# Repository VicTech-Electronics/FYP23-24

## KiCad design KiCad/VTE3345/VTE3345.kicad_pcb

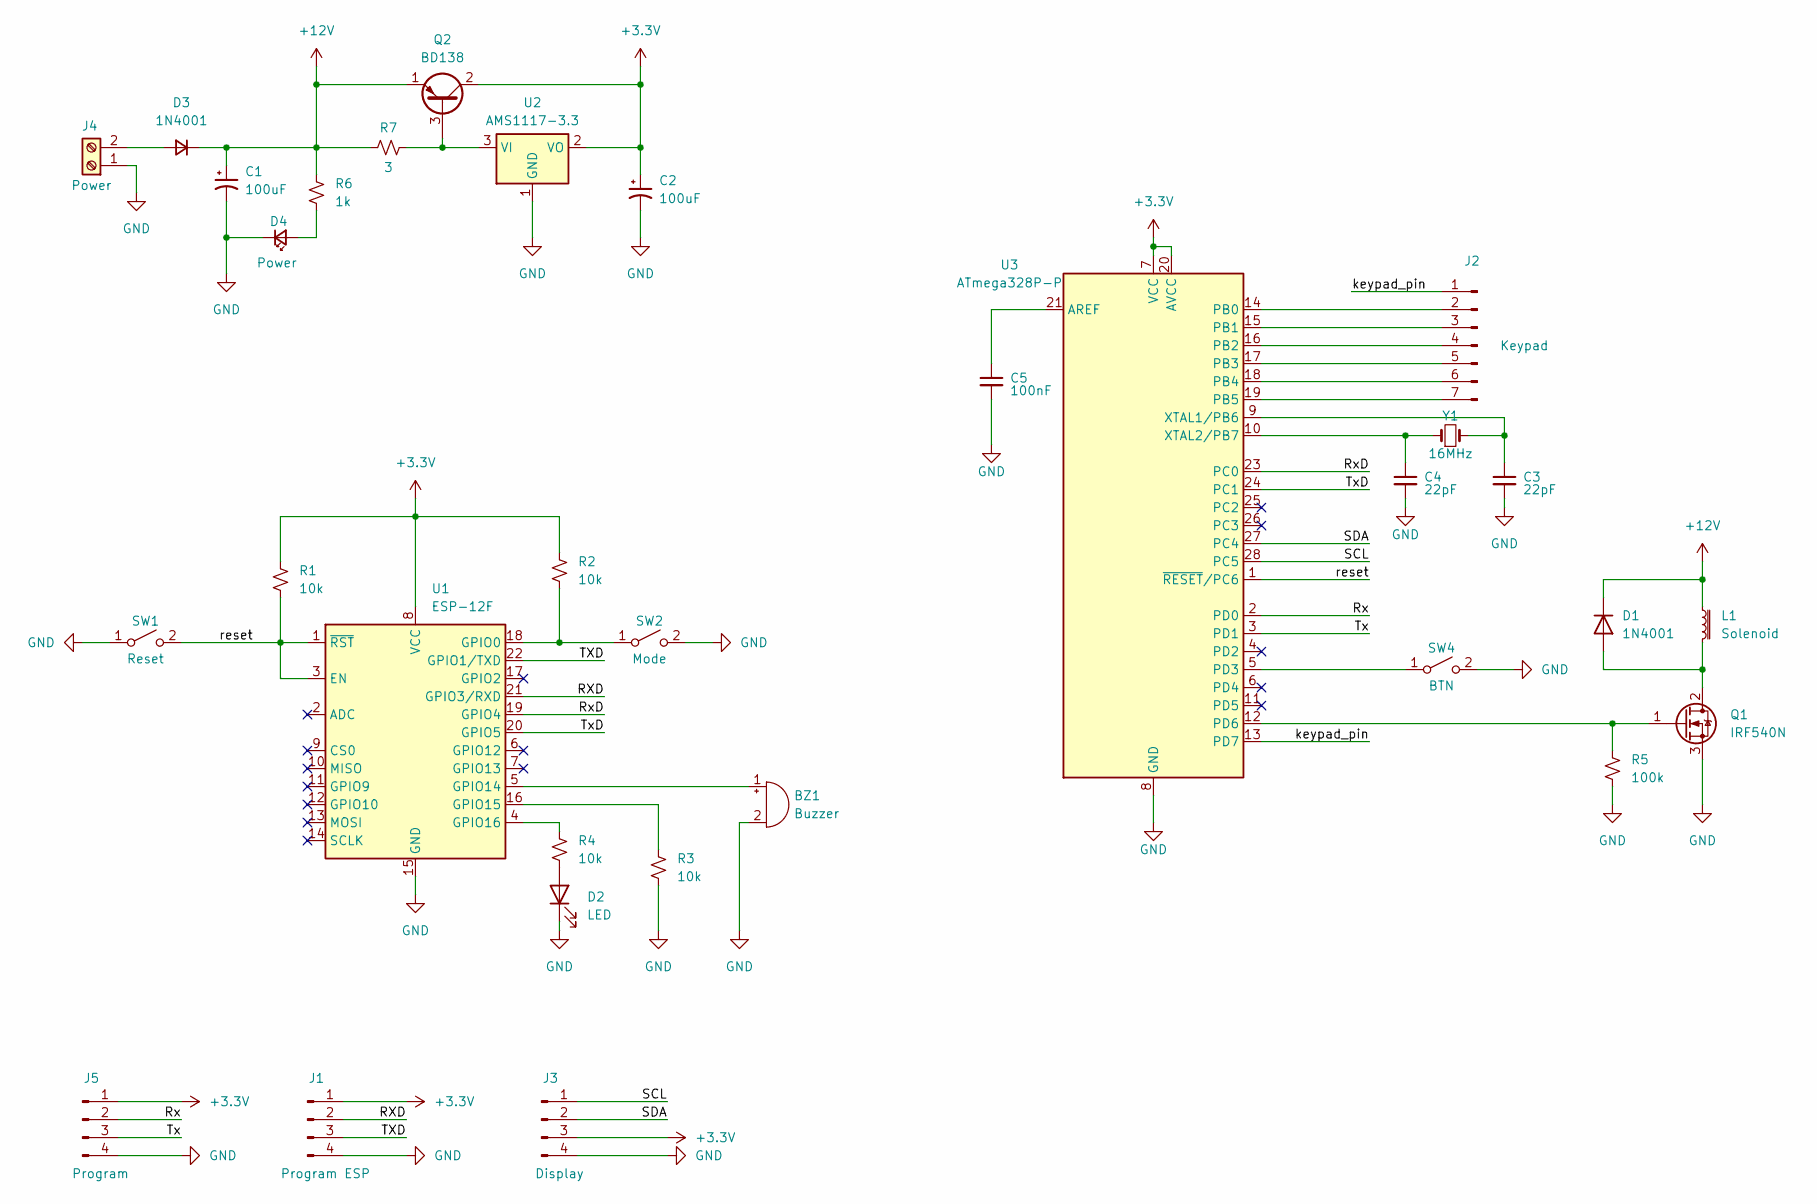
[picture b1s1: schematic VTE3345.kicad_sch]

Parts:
BZ1: Buzzer; Buzzer_12x9.5RM7.6
C1, C2: 100uF; CP_Radial_D5.0mm_P2.50mm
C3, C4: 22pF; C_Disc_D3.0mm_W1.6mm_P2.50mm
C5: 100nF; C_Disc_D3.0mm_W1.6mm_P2.50mm
D1: 1N4001; D_DO-41_SOD81_P10.16mm_Horizontal
D2: LED; LED_D3.0mm
D3: 1N4001; D_A-405_P10.16mm_Horizontal
D4: Power; LED_D3.0mm
J1: Program ESP; PinHeader_1x04_P2.54mm_Vertical
J2: Keypad; PinHeader_1x07_P2.54mm_Vertical
J3: Display; PinHeader_1x04_P2.54mm_Vertical
J4: Power; TerminalBlock_bornier-2_P5.08mm
J5: Program; PinHeader_1x04_P2.54mm_Vertical
L1: Solenoid; TerminalBlock_bornier-2_P5.08mm
Q1: IRF540N; TO-220-3_Vertical
Q2: BD138; TO-126-3_Vertical
R1, R2, R3, R4: 10k; R_Axial_DIN0207_L6.3mm_D2.5mm_P10.16mm_Horizontal
R5: 100k; R_Axial_DIN0207_L6.3mm_D2.5mm_P10.16mm_Horizontal
R6: 1k; R_Axial_DIN0207_L6.3mm_D2.5mm_P10.16mm_Horizontal
R7: 3; R_Axial_DIN0207_L6.3mm_D2.5mm_P10.16mm_Horizontal
SW1: Reset; SW_PUSH_6mm
SW2: Mode; SW_PUSH_6mm
SW4: BTN; TestPoint_2Pads_Pitch2.54mm_Drill0.8mm
U1: ESP-12F; ESP-12E
U2: AMS1117-3.3; SOT-223-3_TabPin2
U3: ATmega328P-P; DIP-28_W7.62mm_LongPads
Y1: 16MHz; Crystal_HC52-U_Vertical

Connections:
+3.3V: C2.1, J1.1, J3.3, J5.1, Q2.2 (C), R1.1, R2.1, U1.8 (VCC), U2.2 (VO), U3.7 (VCC), U3.20 (AVCC)
+12V: C1.1, D1.1 (K), D3.1 (K), L1.1, Q2.1 (E), R6.1, R7.1
/RXD: J1.2, U1.21 (GPIO3/RXD)
/Rx: J5.2, U3.2 (PD0)
/RxD: U1.19 (GPIO4), U3.23 (PC0)
/SCL: J3.1, U3.28 (PC5)
/SDA: J3.2, U3.27 (PC4)
/TXD: J1.3, U1.22 (GPIO1/TXD)
/Tx: J5.3, U3.3 (PD1)
/TxD: U1.20 (GPIO5), U3.24 (PC1)
/keypad_pin: J2.1, U3.13 (PD7)
/reset: R1.2, SW1.2 (B), U1.1 (~RST), U1.3 (EN), U3.1 (~RESET/PC6)
GND: BZ1.2 (-), C1.2, C2.2, C3.2, C4.2, C5.2, D2.1 (K), D4.1 (K), J1.4, J3.4, J4.1, J5.4, Q1.3 (S), R3.2, R5.1, SW1.1 (A), SW2.2 (B), SW4.2 (B), U1.15 (GND), U2.1 (GND), U3.8 (GND), U3.22 (GND)
unnamed: BZ1.1 (+), U1.5 (GPIO14)
unnamed: D1.2 (A), L1.2, Q1.2 (D)
unnamed: D2.2 (A), R4.2
unnamed: D3.2 (A), J4.2
unnamed: D4.2 (A), R6.2
unnamed: J2.2, U3.14 (PB0)
unnamed: J2.3, U3.15 (PB1)
unnamed: J2.4, U3.16 (PB2)
unnamed: J2.5, U3.17 (PB3)
unnamed: J2.6, U3.18 (PB4)
unnamed: J2.7, U3.19 (PB5)
unnamed: Q1.1 (G), R5.2, U3.12 (PD6)
unnamed: Q2.3 (B), R7.2, U2.3 (VI)
unnamed: R2.2, SW2.1 (A), U1.18 (GPIO0)
unnamed: SW4.1 (A), U3.5 (PD3)
unnamed: R3.1, U1.16 (GPIO15)
unnamed: R4.1, U1.4 (GPIO16)
unnamed: C5.1, U3.21 (AREF)
unnamed: C3.1, U3.9 (XTAL1/PB6), Y1.2
unnamed: C4.1, U3.10 (XTAL2/PB7), Y1.1

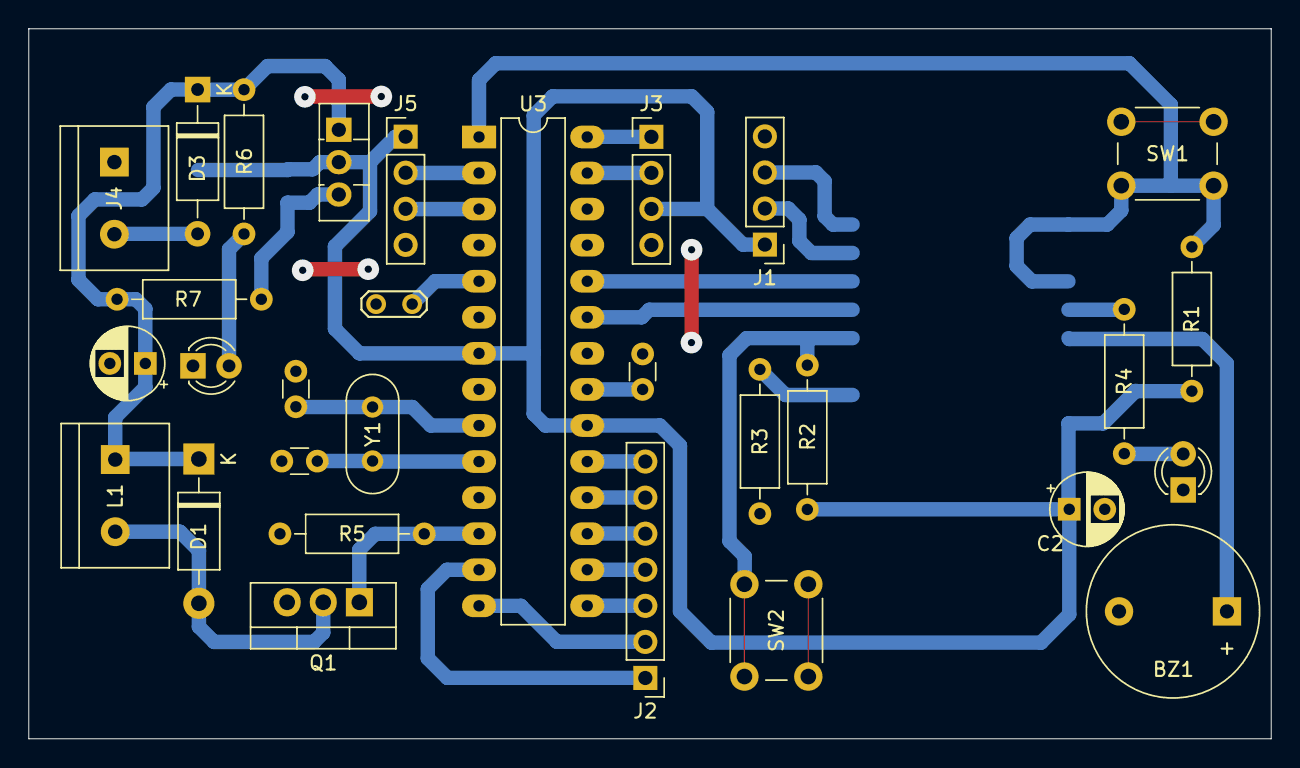
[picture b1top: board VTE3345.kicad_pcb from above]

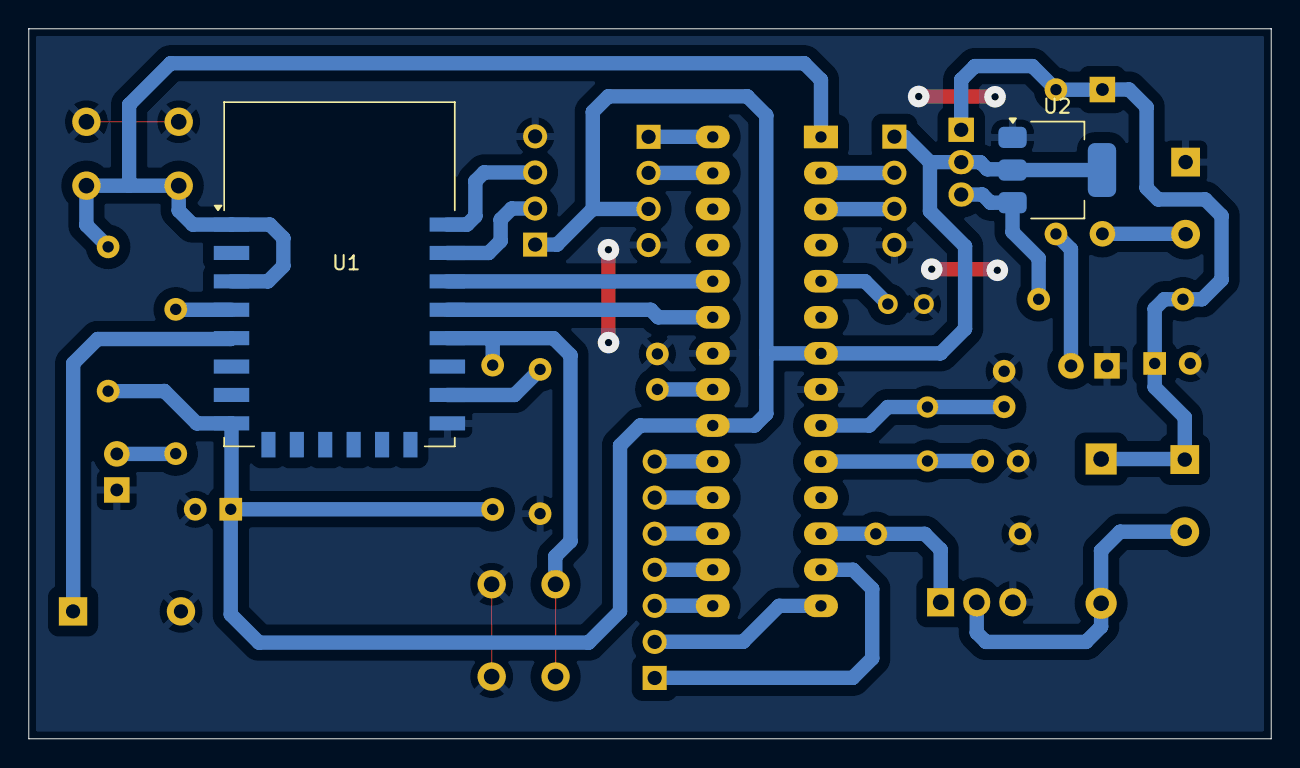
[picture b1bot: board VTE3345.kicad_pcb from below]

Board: 2 copper layers, 87.5 x 50.0 mm, 32 parts (2 on the bottom side), 33 nets.

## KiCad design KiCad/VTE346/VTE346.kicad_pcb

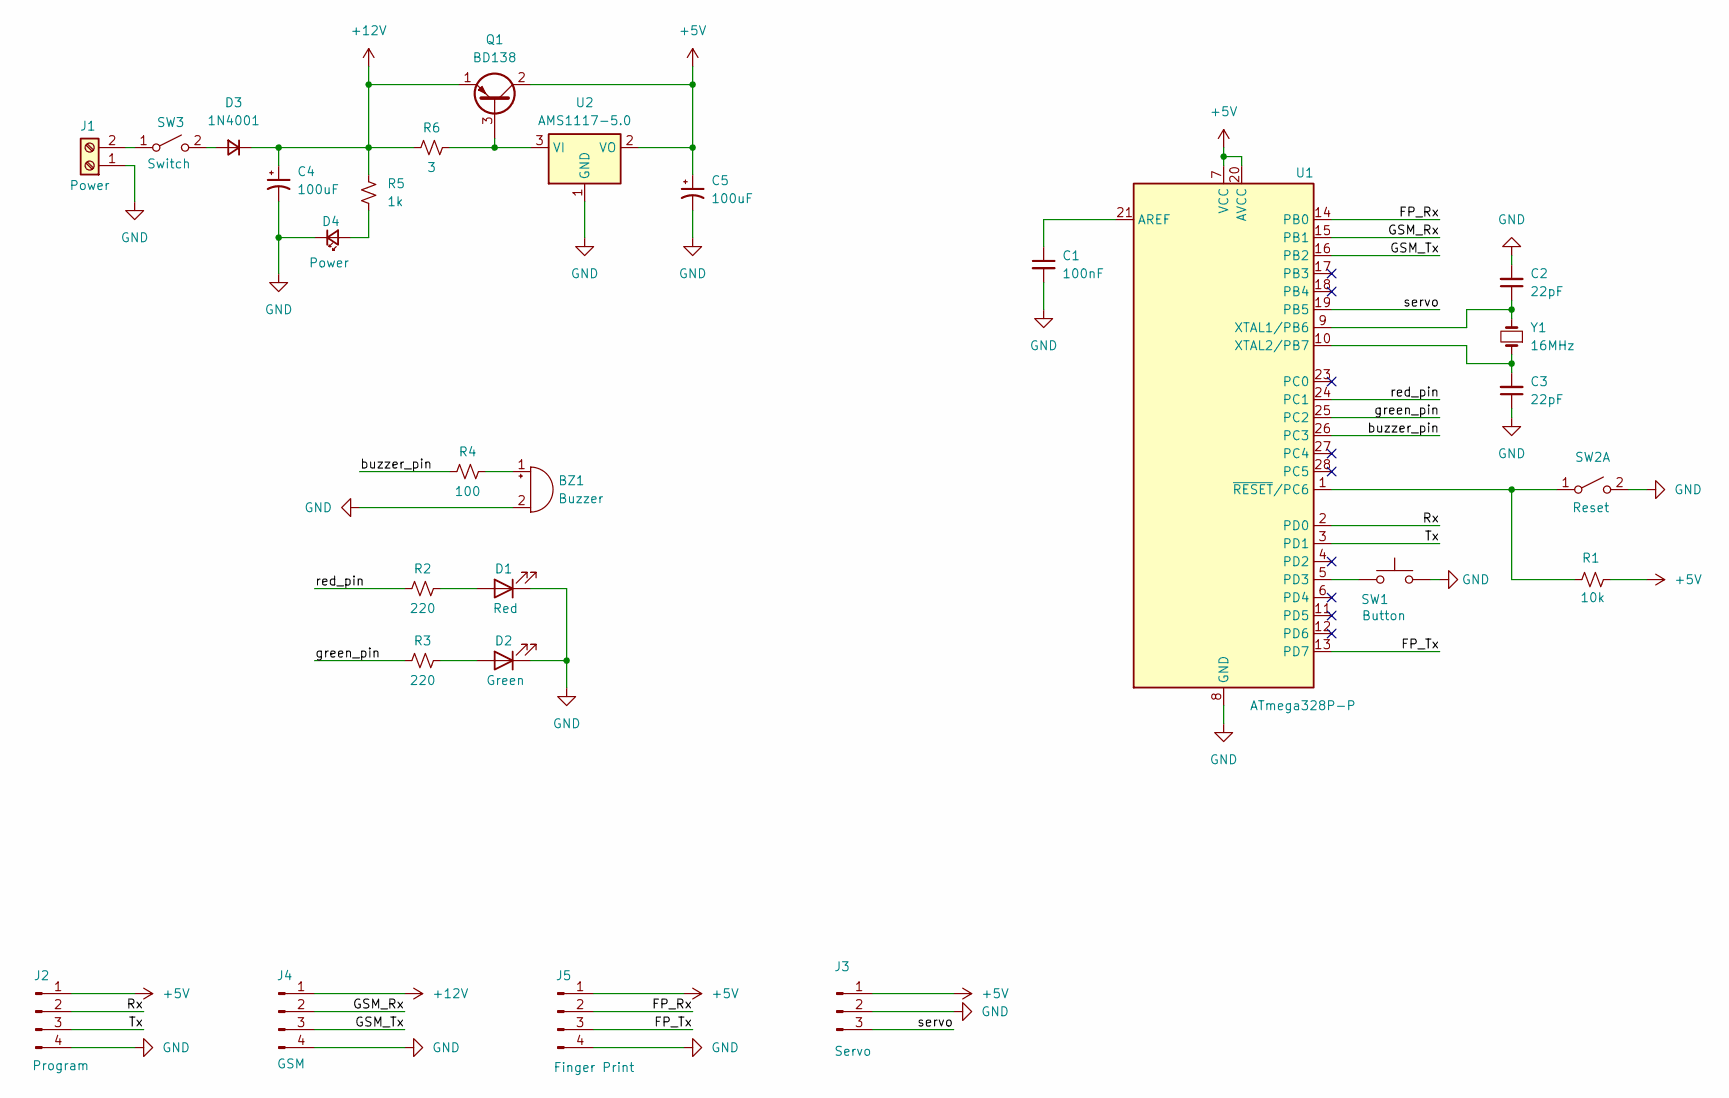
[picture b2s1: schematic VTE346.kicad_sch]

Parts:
BZ1: Buzzer; Buzzer_12x9.5RM7.6
C1: 100nF; C_Disc_D3.0mm_W1.6mm_P2.50mm
C2, C3: 22pF; C_Disc_D3.0mm_W1.6mm_P2.50mm
C4, C5: 100uF; CP_Radial_D5.0mm_P2.50mm
D1: Red; LED_D3.0mm
D2: Green; LED_D3.0mm
D3: 1N4001; D_A-405_P10.16mm_Horizontal
D4: Power; LED_D3.0mm
J1: Power; TerminalBlock_bornier-2_P5.08mm
J2: Program; PinHeader_1x04_P2.54mm_Vertical
J3: Servo; PinHeader_1x03_P2.54mm_Vertical
J4: GSM; PinHeader_1x04_P2.54mm_Vertical
J5: Finger Print; PinHeader_1x04_P2.54mm_Vertical
Q1: BD138; TO-126-3_Vertical
R1: 10k; R_Axial_DIN0207_L6.3mm_D2.5mm_P10.16mm_Horizontal
R2, R3: 220; R_Axial_DIN0207_L6.3mm_D2.5mm_P10.16mm_Horizontal
R4: 100; R_Axial_DIN0207_L6.3mm_D2.5mm_P10.16mm_Horizontal
R5: 1k; R_Axial_DIN0207_L6.3mm_D2.5mm_P10.16mm_Horizontal
R6: 3; R_Axial_DIN0207_L6.3mm_D2.5mm_P10.16mm_Horizontal
SW1: Button; TestPoint_2Pads_Pitch2.54mm_Drill0.8mm
SW2: Reset; SW_PUSH_6mm
SW3: Switch; TestPoint_2Pads_Pitch2.54mm_Drill0.8mm
U1: ATmega328P-P; DIP-28_W7.62mm_Socket_LongPads
U2: AMS1117-5.0; SOT-223-3_TabPin2
Y1: 16MHz; Crystal_HC50_Vertical

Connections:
+5V: C5.1, J2.1, J3.1, J5.1, Q1.2 (C), R1.2, U1.7 (VCC), U1.20 (AVCC), U2.2 (VO)
+12V: C4.1, D3.1 (K), J4.1, Q1.1 (E), R5.1, R6.1
/FP_Rx: J5.2, U1.14 (PB0)
/FP_Tx: J5.3, U1.13 (PD7)
/GSM_Rx: J4.2, U1.15 (PB1)
/GSM_Tx: J4.3, U1.16 (PB2)
/Rx: J2.2, U1.2 (PD0)
/Tx: J2.3, U1.3 (PD1)
/buzzer_pin: R4.1, U1.26 (PC3)
/green_pin: R3.1, U1.25 (PC2)
/red_pin: R2.1, U1.24 (PC1)
/servo: J3.3, U1.19 (PB5)
GND: BZ1.2 (-), C1.2, C2.2, C3.1, C4.2, C5.2, D1.1 (K), D2.1 (K), D4.1 (K), J1.1, J2.4, J3.2, J4.4, J5.4, SW1.2, SW2.2 (B), U1.8 (GND), U1.22 (GND), U2.1 (GND)
unnamed: BZ1.1 (+), R4.2
unnamed: D1.2 (A), R2.2
unnamed: D2.2 (A), R3.2
unnamed: D3.2 (A), SW3.2 (B)
unnamed: D4.2 (A), R5.2
unnamed: J1.2, SW3.1 (A)
unnamed: Q1.3 (B), R6.2, U2.3 (VI)
unnamed: R1.1, SW2.1 (A), U1.1 (~RESET/PC6)
unnamed: C1.1, U1.21 (AREF)
unnamed: SW1.1, U1.5 (PD3)
unnamed: C2.1, U1.9 (XTAL1/PB6), Y1.2
unnamed: C3.2, U1.10 (XTAL2/PB7), Y1.1

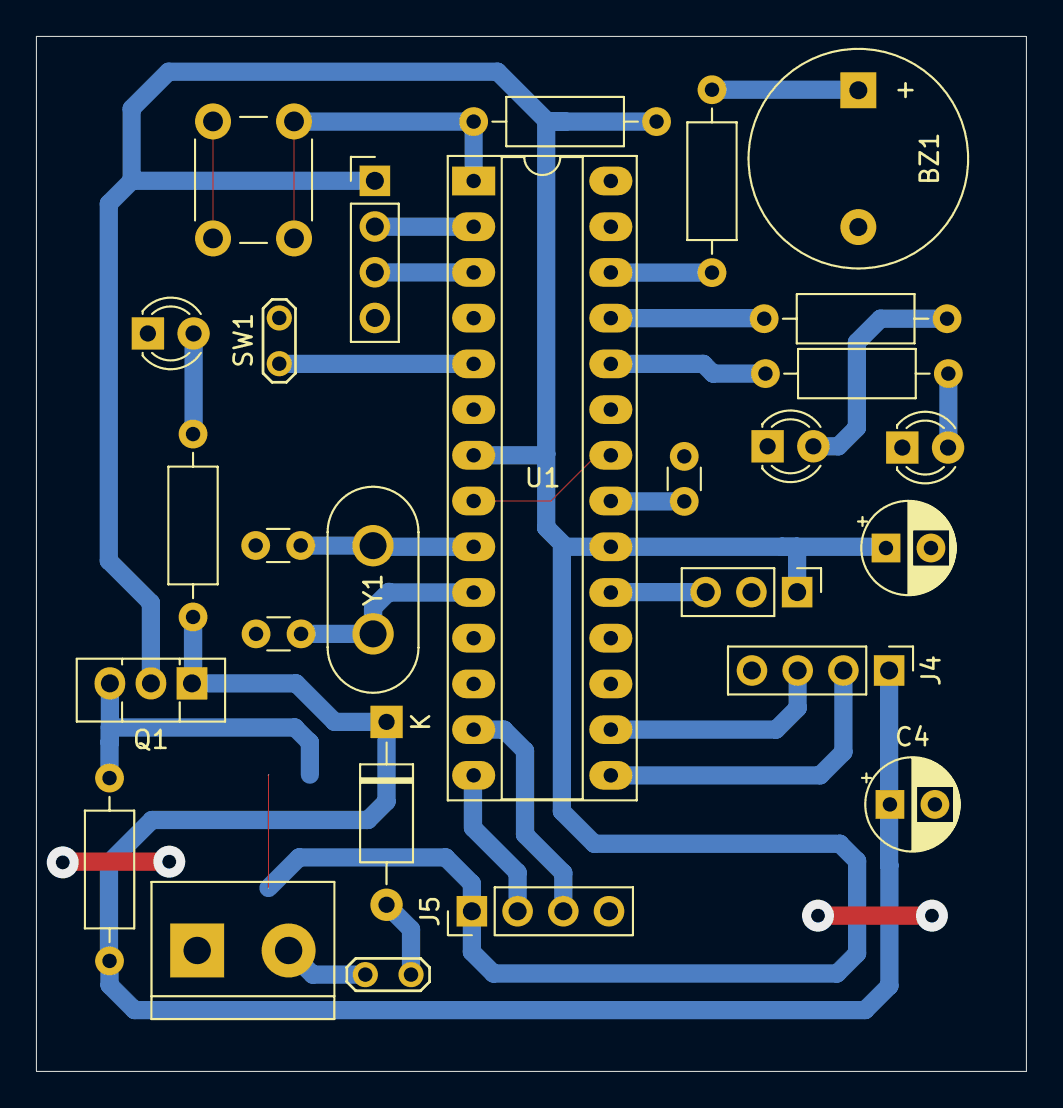
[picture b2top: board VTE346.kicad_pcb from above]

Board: 2 copper layers, 55.0 x 57.5 mm, 28 parts (1 on the bottom side), 25 nets.

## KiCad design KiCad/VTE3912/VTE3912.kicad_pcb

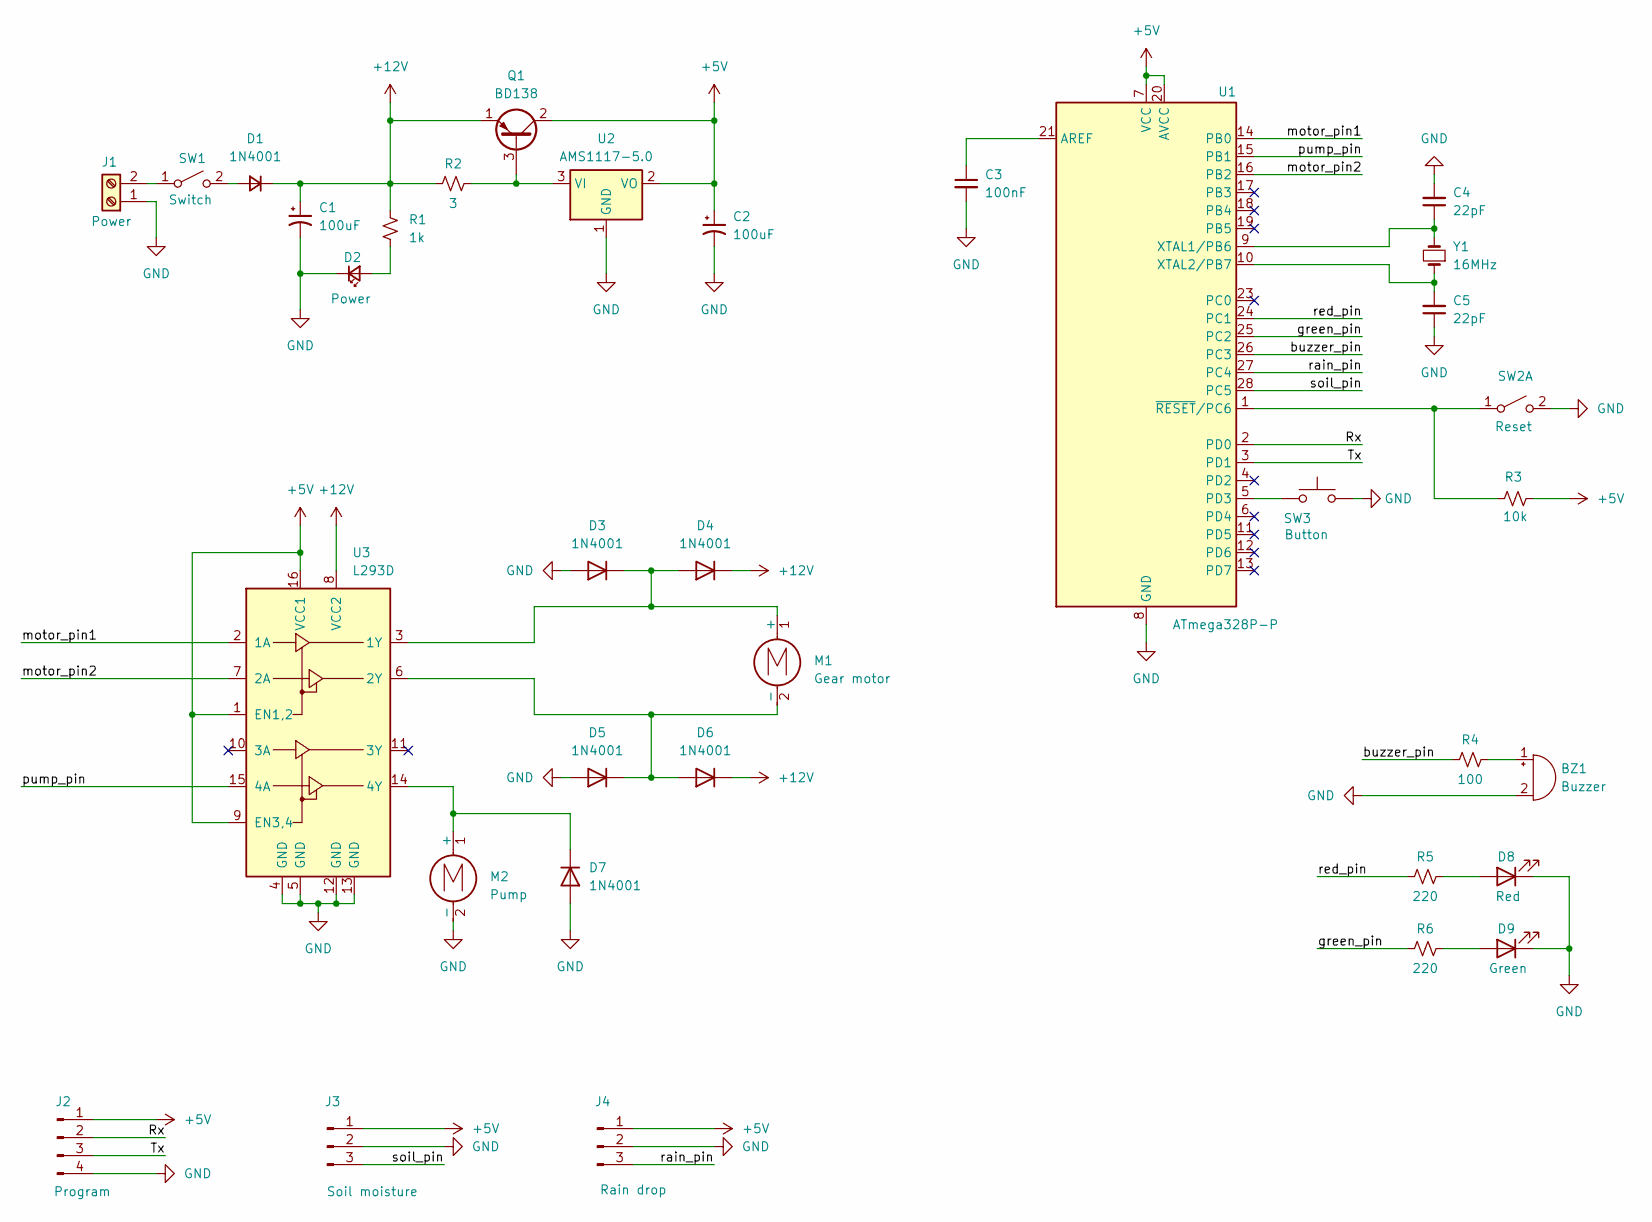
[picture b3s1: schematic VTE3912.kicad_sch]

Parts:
BZ1: Buzzer; Buzzer_12x9.5RM7.6
C1, C2: 100uF; CP_Radial_D5.0mm_P2.50mm
C3: 100nF; C_Disc_D3.0mm_W1.6mm_P2.50mm
C4, C5: 22pF; C_Disc_D3.0mm_W1.6mm_P2.50mm
D1: 1N4001; D_A-405_P10.16mm_Horizontal
D2: Power; LED_D3.0mm
D3, D4, D5, D6, D7: 1N4001; D_DO-41_SOD81_P10.16mm_Horizontal
D8: Red; LED_D3.0mm
D9: Green; LED_D3.0mm
J1: Power; TerminalBlock_bornier-2_P5.08mm
J2: Program; PinHeader_1x04_P2.54mm_Vertical
J3: Soil moisture; PinHeader_1x03_P2.54mm_Vertical
J4: Rain drop; PinHeader_1x03_P2.54mm_Vertical
M1: Gear motor; TerminalBlock_bornier-2_P5.08mm
M2: Pump; TerminalBlock_bornier-2_P5.08mm
Q1: BD138; TO-126-3_Vertical
R1: 1k; R_Axial_DIN0207_L6.3mm_D2.5mm_P10.16mm_Horizontal
R2: 3; R_Axial_DIN0207_L6.3mm_D2.5mm_P10.16mm_Horizontal
R3: 10k; R_Axial_DIN0207_L6.3mm_D2.5mm_P10.16mm_Horizontal
R4: 100; R_Axial_DIN0207_L6.3mm_D2.5mm_P10.16mm_Horizontal
R5, R6: 220; R_Axial_DIN0207_L6.3mm_D2.5mm_P10.16mm_Horizontal
SW1: Switch; TestPoint_2Pads_Pitch2.54mm_Drill0.8mm
SW2: Reset; SW_PUSH_6mm
SW3: Button; TestPoint_2Pads_Pitch2.54mm_Drill0.8mm
U1: ATmega328P-P; DIP-28_W7.62mm_Socket_LongPads
U2: AMS1117-5.0; SOT-223-3_TabPin2
U3: L293D; DIP-16_W7.62mm
Y1: 16MHz; Crystal_HC50_Vertical

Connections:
+5V: C2.1, J2.1, J3.1, J4.1, Q1.2 (C), R3.2, U1.7 (VCC), U1.20 (AVCC), U2.2 (VO), U3.1 (EN1,2), U3.9 (EN3,4), U3.16 (VCC1)
+12V: C1.1, D1.1 (K), D4.1 (K), D6.1 (K), Q1.1 (E), R1.1, R2.1, U3.8 (VCC2)
/Rx: J2.2, U1.2 (PD0)
/Tx: J2.3, U1.3 (PD1)
/buzzer_pin: R4.1, U1.26 (PC3)
/green_pin: R6.1, U1.25 (PC2)
/motor_pin1: U1.14 (PB0), U3.2 (1A)
/motor_pin2: U1.16 (PB2), U3.7 (2A)
/pump_pin: U1.15 (PB1), U3.15 (4A)
/rain_pin: J4.3, U1.27 (PC4)
/red_pin: R5.1, U1.24 (PC1)
/soil_pin: J3.3, U1.28 (PC5)
GND: BZ1.2 (-), C1.2, C2.2, C3.2, C4.2, C5.1, D2.1 (K), D3.2 (A), D5.2 (A), D7.2 (A), D8.1 (K), D9.1 (K), J1.1, J2.4, J3.2, J4.2, M2.2 (-), SW2.2 (B), SW3.2, U1.8 (GND), U1.22 (GND), U2.1 (GND), U3.4 (GND), U3.5 (GND), U3.12 (GND), U3.13 (GND)
unnamed: BZ1.1 (+), R4.2
unnamed: D1.2 (A), SW1.2 (B)
unnamed: D2.2 (A), R1.2
unnamed: D3.1 (K), D4.2 (A), M1.1 (+), U3.3 (1Y)
unnamed: D5.1 (K), D6.2 (A), M1.2 (-), U3.6 (2Y)
unnamed: D7.1 (K), M2.1 (+), U3.14 (4Y)
unnamed: D8.2 (A), R5.2
unnamed: D9.2 (A), R6.2
unnamed: J1.2, SW1.1 (A)
unnamed: Q1.3 (B), R2.2, U2.3 (VI)
unnamed: R3.1, SW2.1 (A), U1.1 (~RESET/PC6)
unnamed: C3.1, U1.21 (AREF)
unnamed: SW3.1, U1.5 (PD3)
unnamed: C4.1, U1.9 (XTAL1/PB6), Y1.2
unnamed: C5.2, U1.10 (XTAL2/PB7), Y1.1

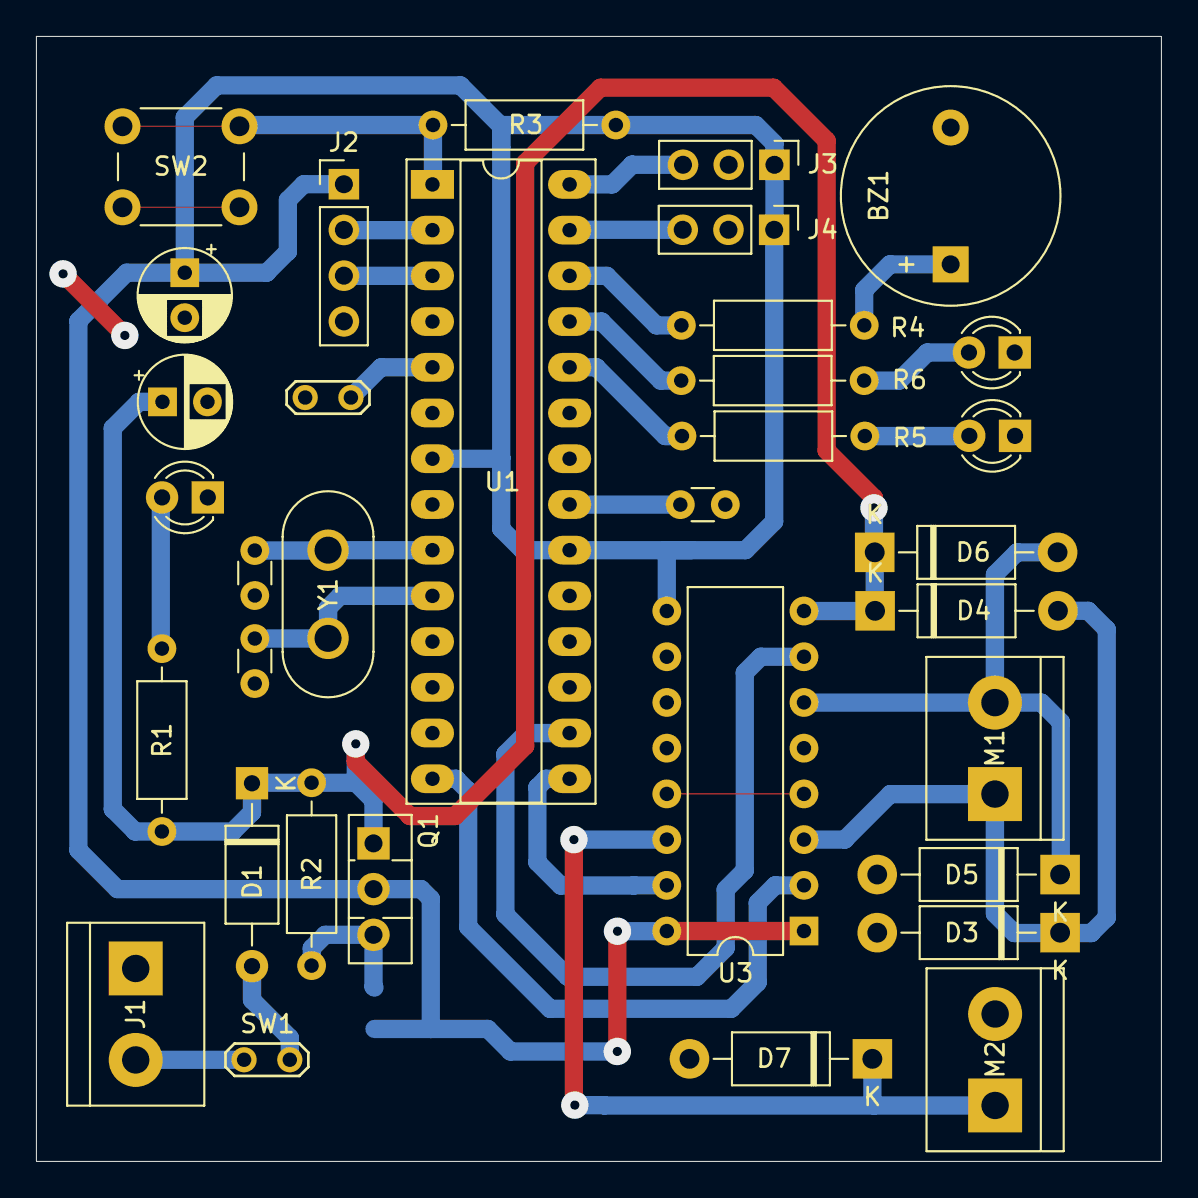
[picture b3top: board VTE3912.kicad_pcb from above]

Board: 2 copper layers, 62.5 x 62.5 mm, 35 parts (1 on the bottom side), 28 nets.

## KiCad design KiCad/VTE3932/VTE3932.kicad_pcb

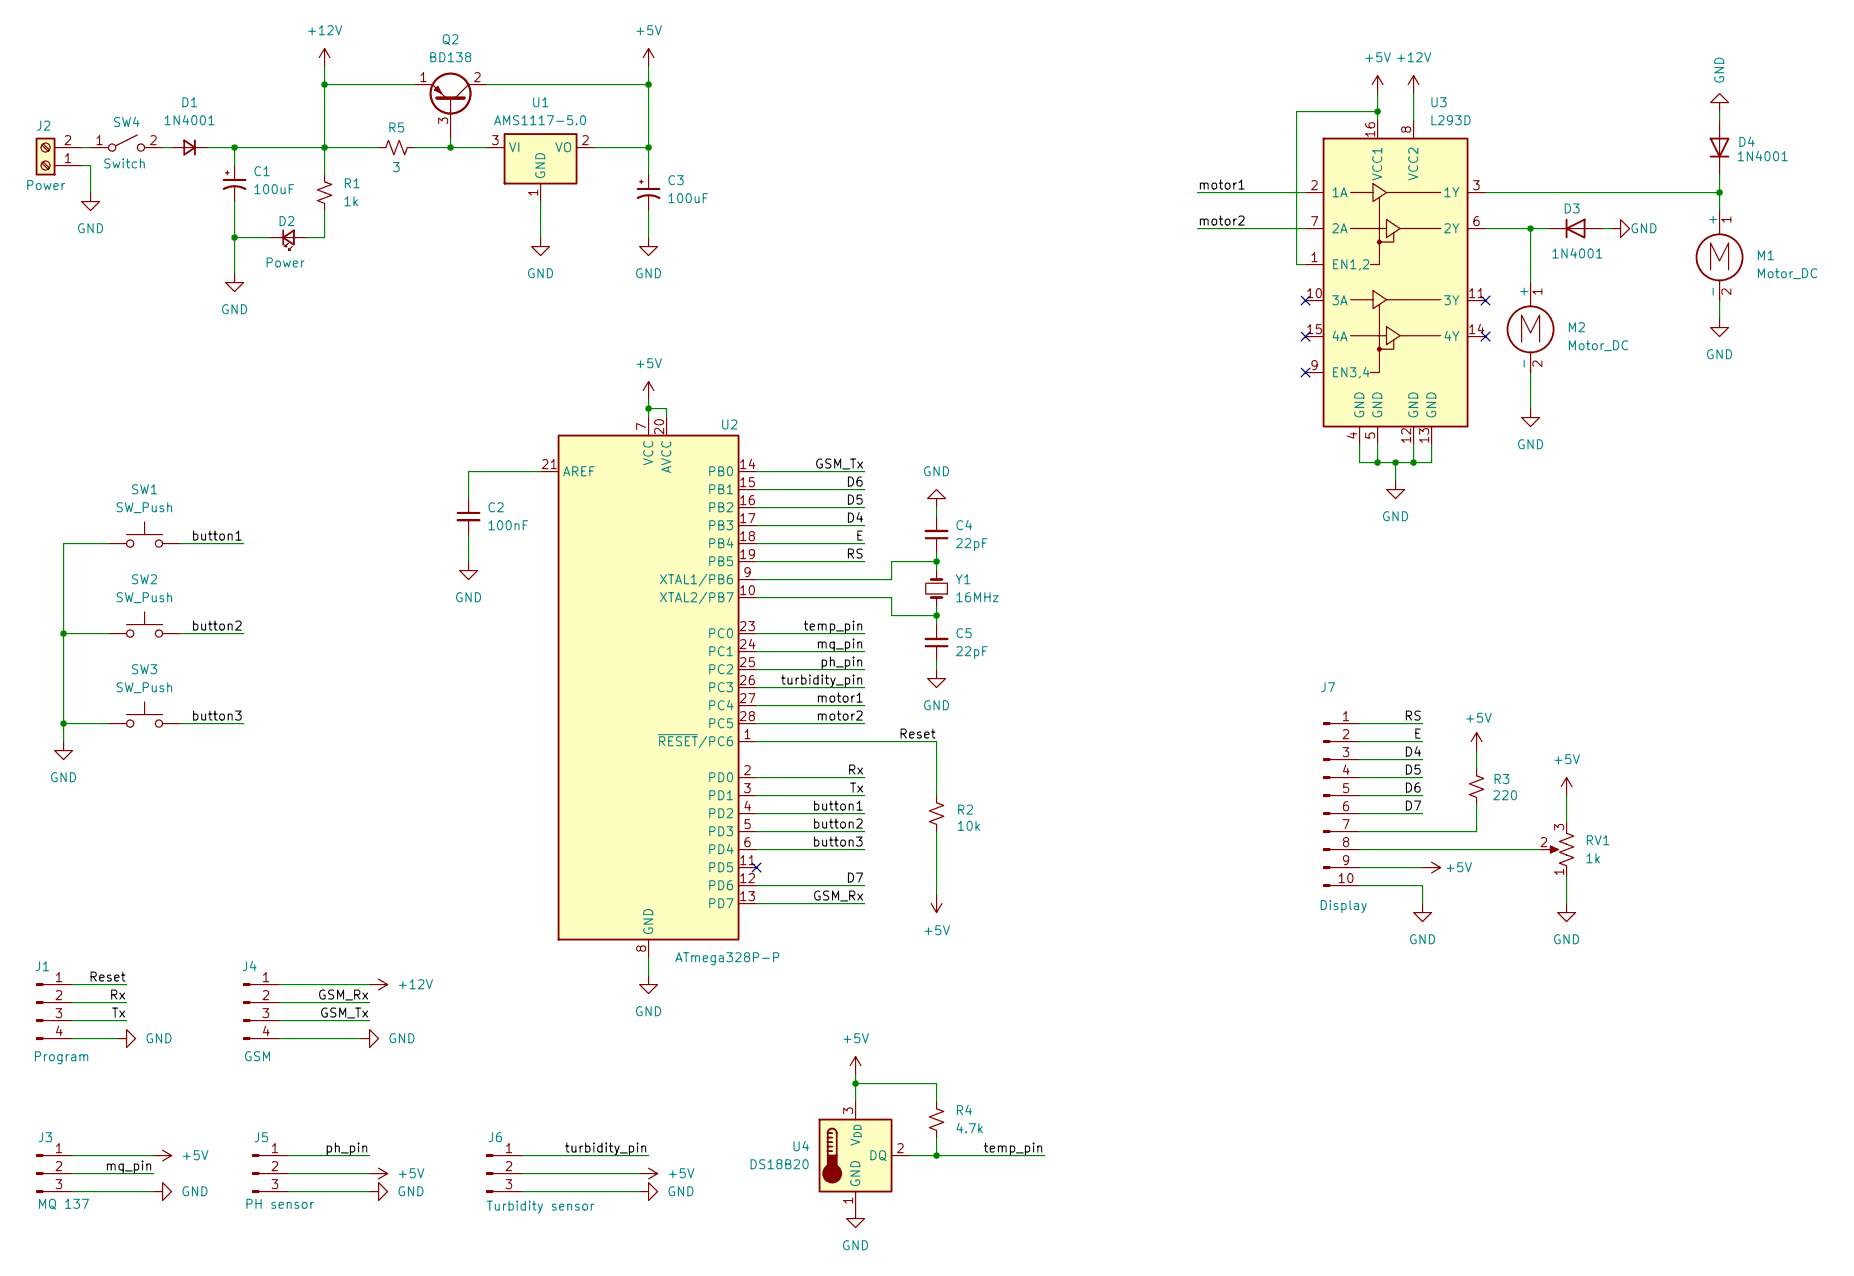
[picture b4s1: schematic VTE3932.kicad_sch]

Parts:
C1, C3: 100uF; CP_Radial_D5.0mm_P2.50mm
C2: 100nF; C_Disc_D3.0mm_W1.6mm_P2.50mm
C4, C5: 22pF; C_Disc_D3.0mm_W1.6mm_P2.50mm
D1: 1N4001; D_A-405_P10.16mm_Horizontal
D2: Power; LED_D3.0mm
D3, D4: 1N4001; D_DO-41_SOD81_P10.16mm_Horizontal
J1: Program; PinHeader_1x04_P2.54mm_Vertical
J2: Power; TerminalBlock_bornier-2_P5.08mm
J3: MQ 137; PinHeader_1x03_P2.54mm_Vertical
J4: GSM; PinHeader_1x04_P2.54mm_Vertical
J5: PH sensor; PinHeader_1x03_P2.54mm_Vertical
J6: Turbidity sensor; PinHeader_1x03_P2.54mm_Vertical
J7: Display; PinHeader_1x10_P2.54mm_Vertical
M1, M2: Motor_DC; TerminalBlock_bornier-2_P5.08mm
Q2: BD138; TO-126-3_Vertical
R1: 1k; R_Axial_DIN0207_L6.3mm_D2.5mm_P10.16mm_Horizontal
R2: 10k; R_Axial_DIN0207_L6.3mm_D2.5mm_P10.16mm_Horizontal
R3: 220; R_Axial_DIN0207_L6.3mm_D2.5mm_P10.16mm_Horizontal
R4: 4.7k; R_Axial_DIN0207_L6.3mm_D2.5mm_P10.16mm_Horizontal
R5: 3; R_Axial_DIN0207_L6.3mm_D2.5mm_P10.16mm_Horizontal
RV1: 1k; Potentiometer_Runtron_RM-065_Vertical
SW1, SW2, SW3: SW_Push; TestPoint_2Pads_Pitch2.54mm_Drill0.8mm
SW4: Switch; TestPoint_2Pads_Pitch2.54mm_Drill0.8mm
U1: AMS1117-5.0; SOT-223-3_TabPin2
U2: ATmega328P-P; DIP-28_W7.62mm_Socket_LongPads
U3: L293D; DIP-16_W7.62mm_Socket_LongPads
U4: DS18B20; TO-92_Inline
Y1: 16MHz; Crystal_HC50_Vertical

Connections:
+5V: C3.1, J3.1, J5.2, J6.2, J7.9, Q2.2 (C), R2.2, R3.2, R4.1, RV1.3, U1.2 (VO), U2.7 (VCC), U2.20 (AVCC), U3.1 (EN1,2), U3.16 (VCC1), U4.3 (V_{DD})
+12V: C1.1, D1.1 (K), J4.1, Q2.1 (E), R1.1, R5.1, U3.8 (VCC2)
/D4: J7.3, U2.17 (PB3)
/D5: J7.4, U2.16 (PB2)
/D6: J7.5, U2.15 (PB1)
/D7: J7.6, U2.12 (PD6)
/E: J7.2, U2.18 (PB4)
/GSM_Rx: J4.2, U2.13 (PD7)
/GSM_Tx: J4.3, U2.14 (PB0)
/RS: J7.1, U2.19 (PB5)
/Reset: J1.1, R2.1, U2.1 (~RESET/PC6)
/Rx: J1.2, U2.2 (PD0)
/Tx: J1.3, U2.3 (PD1)
/button1: SW1.2, U2.4 (PD2)
/button2: SW2.2, U2.5 (PD3)
/button3: SW3.2, U2.6 (PD4)
/motor1: U2.27 (PC4), U3.2 (1A)
/motor2: U2.28 (PC5), U3.7 (2A)
/mq_pin: J3.2, U2.24 (PC1)
/ph_pin: J5.1, U2.25 (PC2)
/temp_pin: R4.2, U2.23 (PC0), U4.2 (DQ)
/turbidity_pin: J6.1, U2.26 (PC3)
GND: C1.2, C2.2, C3.2, C4.2, C5.1, D2.1 (K), D3.2 (A), D4.2 (A), J1.4, J2.1, J3.3, J4.4, J5.3, J6.3, J7.10, M1.2 (-), M2.2 (-), RV1.1, SW1.1, SW2.1, SW3.1, U1.1 (GND), U2.8 (GND), U2.22 (GND), U3.4 (GND), U3.5 (GND), U3.12 (GND), U3.13 (GND), U4.1 (GND)
unnamed: D1.2 (A), SW4.2 (B)
unnamed: D2.2 (A), R1.2
unnamed: D3.1 (K), M2.1 (+), U3.6 (2Y)
unnamed: D4.1 (K), M1.1 (+), U3.3 (1Y)
unnamed: J2.2, SW4.1 (A)
unnamed: J7.7, R3.1
unnamed: J7.8, RV1.2
unnamed: Q2.3 (B), R5.2, U1.3 (VI)
unnamed: C2.1, U2.21 (AREF)
unnamed: C4.1, U2.9 (XTAL1/PB6), Y1.2
unnamed: C5.2, U2.10 (XTAL2/PB7), Y1.1

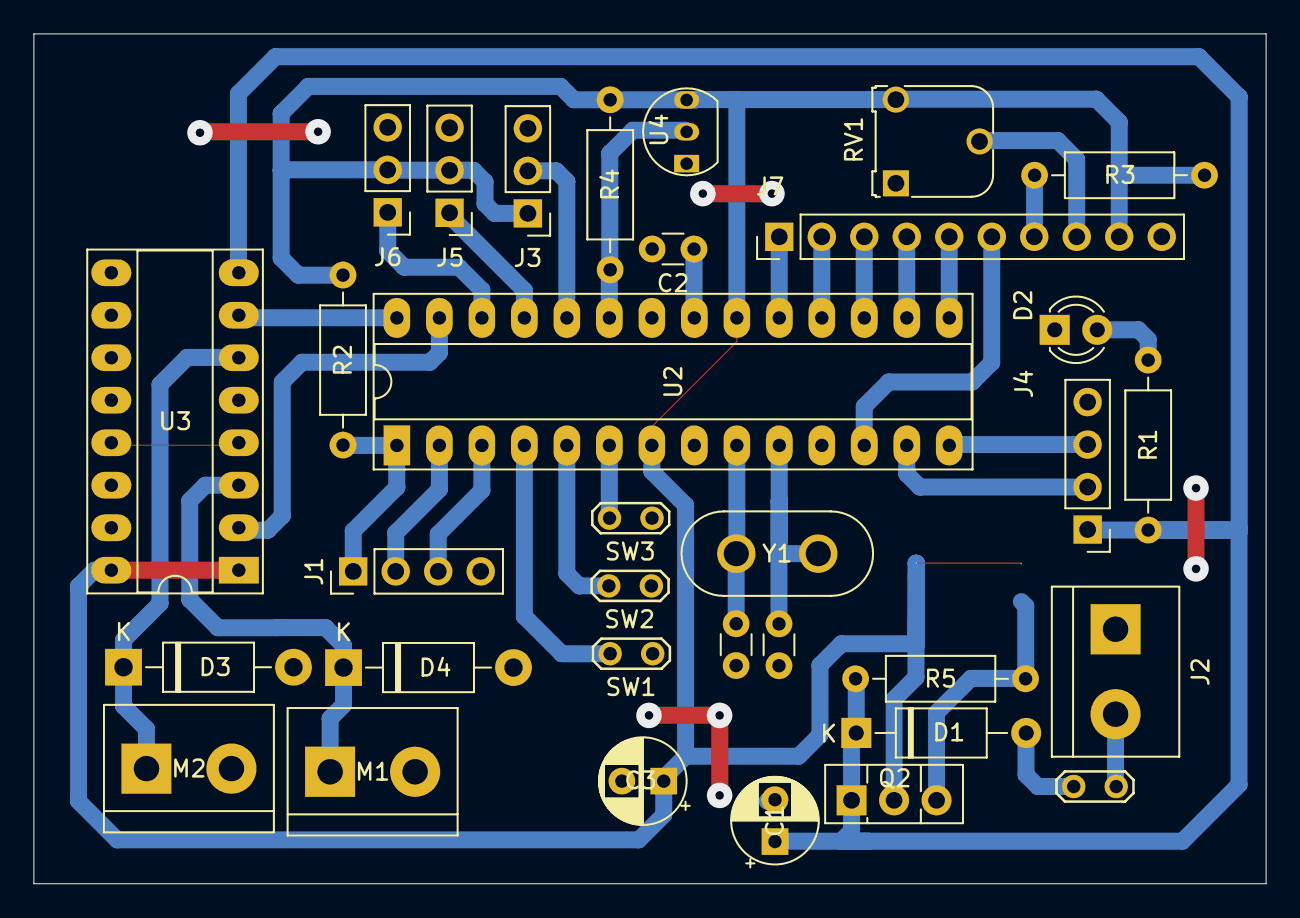
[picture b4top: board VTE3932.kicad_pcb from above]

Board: 2 copper layers, 73.7 x 50.8 mm, 34 parts (1 on the bottom side), 34 nets.
